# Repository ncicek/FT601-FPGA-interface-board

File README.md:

# FTDI FT601 breakout board

A PCB for interfacing FT601 with Lattice MachXO3 Starter Board.
Examples of C driver and Python driver can be found in driver folder.
Verilog and cocotb sims are in fpga folder.

# PCB:

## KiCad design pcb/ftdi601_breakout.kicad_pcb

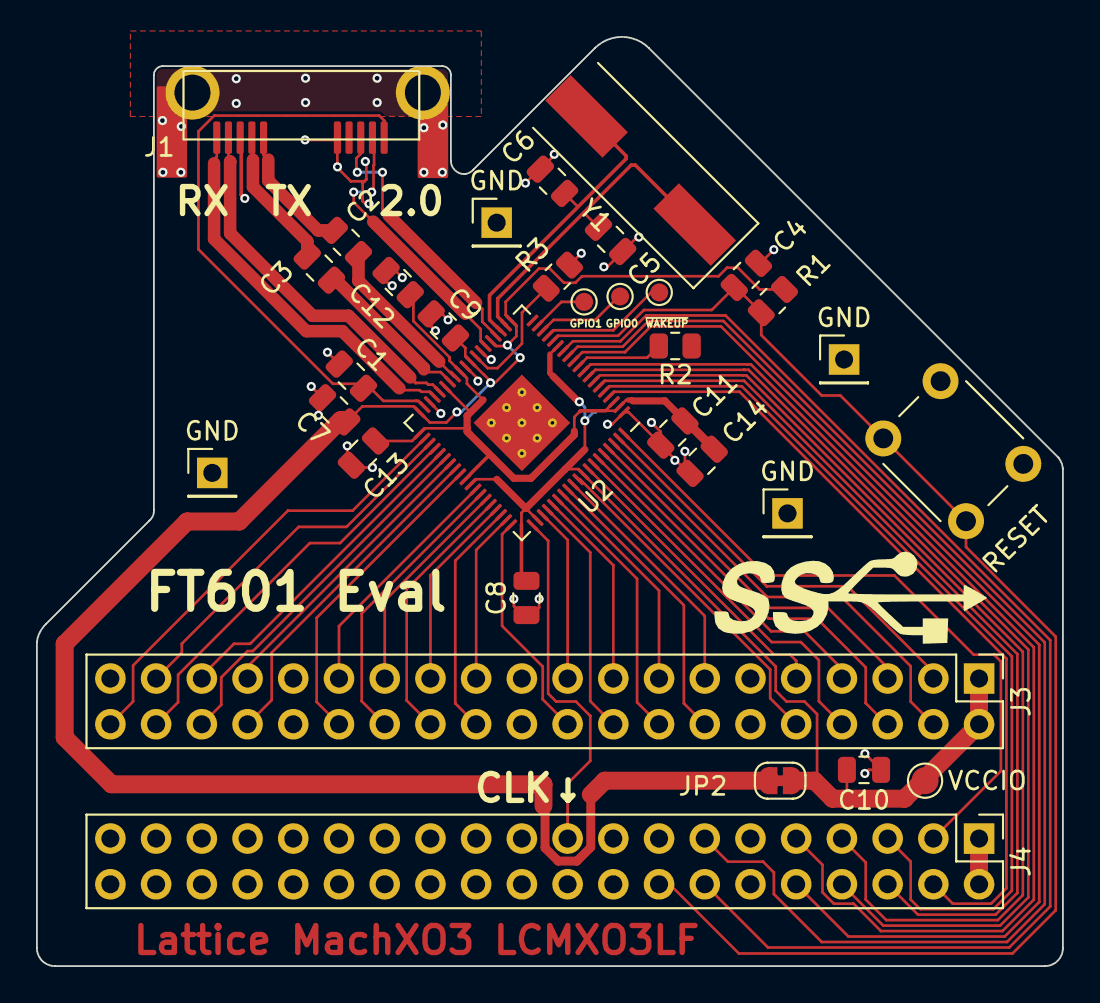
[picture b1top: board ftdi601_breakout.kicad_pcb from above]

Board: 2 copper layers, 57.0 x 51.6 mm, 32 parts (1 on the bottom side), 63 nets.

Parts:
C1, C2, C3, C4, C7, C8, C9, C10, C11, C12, C13, C15: 0.1u; C_0805_2012Metric
C5, C6: 10p; C_0805_2012Metric
C14: 4.7u; C_0805_2012Metric
GND: TestPoint; PinHeader_1x01_P2.54mm_Vertical
GND#2, GND#3, GND#4: TestPoint; PinHeader_1x01_P2.54mm_Vertical
GPIO0, GPIO1: TestPoint; TestPoint_Pad_D1.0mm
J1: USB3_B; usb_microb_3.0
J3: J3 - BANK0; PinHeader_2x20_P2.54mm_Vertical
J4: J4 - BANK1; PinHeader_2x20_P2.54mm_Vertical
JP2: SolderJumper_2_Bridged; SolderJumper-2_P1.3mm_Bridged_RoundedPad1.0x1.5mm
R1, R2: 10k; R_0805_2012Metric
R3: 1.6k; R_0805_2012Metric
RESET: SW_Push; SW_PUSH_6mm
U2: FT601Q-B-T; QFN-76-1EP_9x9mm_P0.4mm_EP3.8x3.8mm_ThermalVias
VCCIO: TestPoint; TestPoint_Pad_D1.5mm
Y1: 30MHz CX3225SB30000H0FLJCC; Crystal_SMD_HC49-SD

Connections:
+1V0: C11.2, C12.2, C13.2, C14.2, U2.2 (AVDD), U2.3 (VD10), U2.30 (VD10), U2.33 (VD10), U2.39 (DV10), U2.48 (VD10)
+3V3: C7.2, C9.2, JP2.2 (B), R1.2, R2.2, U2.20 (VCC33), U2.24 (VCC33), U2.28 (VDDA), U2.38 (VCC33)
+5V: C1.1, J1.1 (VBUS), U2.37 (VBUS)
/BE_0: J4.4, U2.4 (BE_0)
/BE_1: J4.5, U2.5 (BE_1)
/BE_2: J4.6, U2.6 (BE_2)
/BE_3: J4.7, U2.7 (BE_3)
/D+: J1.3 (D+), U2.23 (DP)
/D-: J1.2 (D-), U2.25 (DM)
/DATA_0: J3.40, U2.40 (DATA_0)
/DATA_1: J3.37, U2.41 (DATA_1)
/DATA_2: J3.38, U2.42 (DATA_2)
/DATA_3: J3.35, U2.43 (DATA_3)
/DATA_4: J3.36, U2.44 (DATA_4)
/DATA_5: J3.33, U2.45 (DATA_5)
/DATA_6: J3.34, U2.46 (DATA_6)
/DATA_7: J3.30, U2.47 (DATA_7)
/DATA_8: J3.29, U2.50 (DATA_8)
/DATA_9: J3.28, U2.51 (DATA_9)
/DATA_10: J3.27, U2.52 (DATA_10)
/DATA_11: J3.26, U2.53 (DATA_11)
/DATA_12: J3.25, U2.54 (DATA_12)
/DATA_13: J3.24, U2.55 (DATA_13)
/DATA_14: J3.23, U2.56 (DATA_14)
/DATA_15: J3.20, U2.57 (DATA_15)
/DATA_16: J3.19, U2.60 (DATA_16)
/DATA_17: J3.18, U2.61 (DATA_17)
/DATA_18: J3.17, U2.62 (DATA_18)
/DATA_19: J3.16, U2.63 (DATA_19)
/DATA_20: J3.15, U2.64 (DATA_20)
/DATA_21: J3.14, U2.65 (DATA_21)
/DATA_22: J3.13, U2.66 (DATA_22)
/DATA_23: J3.10, U2.67 (DATA_23)
/DATA_24: J3.9, U2.69 (DATA_24)
/DATA_25: J3.8, U2.70 (DATA_25)
/DATA_26: J3.7, U2.71 (DATA_26)
/DATA_27: J3.6, U2.72 (DATA_27)
/DATA_28: J3.5, U2.73 (DATA_28)
/DATA_29: J3.4, U2.74 (DATA_29)
/DATA_30: J3.3, U2.75 (DATA_30)
/DATA_31: J4.3, U2.76 (DATA_31)
/FTDI_FIFO_CLK_OUT: J4.19, U2.58 (CLK)
/GPIO0: GPIO0.1, U2.17 (GPIO0)
/GPIO1: GPIO1.1, U2.18 (GPIO1)
/USB_RX+: J1.9 (SSRX+), U2.35 (RIDP)
/USB_RX-: J1.8 (SSRX-), U2.34 (RIDN)
/USB_TX+: C3.1, U2.32 (T0DP)
/USB_TX-: C2.1, U2.31 (T0DN)
/USB_TX_cap+: C3.2, J1.6 (SSTX+)
/USB_TX_cap-: C2.2, J1.5 (SSTX-)
/VCCIO0: C8.2, C10.2, C15.2, J3.1, J3.2, JP2.1 (A), U2.14 (VCCIO), U2.49 (VCCIO), U2.59 (VCCIO), U2.68 (VCCIO), VCCIO.1
/VCCIO1: J4.1, J4.2
/XTAL_N: C6.1, U2.22 (XO), Y1.2
/XTAL_P: C5.1, U2.21 (XI), Y1.1
/~OE: J4.14, U2.13 (OE_N)
/~RD: J4.13, U2.12 (RD_N)
/~RESET: C4.1, J4.16, R1.1, RESET.2, U2.15 (RESET_N)
/~RXF: J4.9, U2.9 (RXF_N)
/~TXE: J4.8, U2.8 (TXE_N)
/~WR: J4.10, U2.11 (WR_N)
GND: C1.2, C4.2, C5.2, C6.2, C7.1, C8.1, C9.1, C10.1, C11.1, C12.1, C13.1, C14.1, C15.1, GND.1, GND#2.1, GND#3.1, GND#4.1, J1.4 (GND), J1.7 (DRAIN), J1.10 (SHIELD), J3.11, J3.12, J3.21, J3.22, J3.31, J3.32, J3.39, J4.11, J4.12, J4.21, J4.22, J4.31, J4.32, R3.2, RESET.1, U2.1 (GND), U2.26 (GND), U2.29 (GND), U2.36 (GND), U2.77 (EXP)
unnamed: R2.1, U2.10 (SIWU_N)
unnamed: R3.1, U2.27 (RREF)

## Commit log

2023-05-12 Latest fpga updates
2023-05-12 Latest driver updates
2023-05-12 Documentation
